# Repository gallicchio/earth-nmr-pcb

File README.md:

# Earth's Field NMR — a proton precession magnetometer on one board

Polarize the protons in a litre of water with a current through a coil, switch
the current off faster than they can follow, and listen: they precess about the
Earth's magnetic field at a couple of kilohertz and induce about a microvolt in the
same coil for a second or two.  This board does all of it — the polarizing switch,
the relay that hands the coil from the supply to the receiver, the tuned tank, a
low-noise preamplifier, the filters, the gain, and the sequencer that times it —
on a 243 x 150 mm, four layers printed circuit board whose silkscreen *is* the
schematic, with a headphone jack to hear the protons as well as see them.  Here in Claremont (Harvey Mudd, IGRF-14: 46.0 µT) the Larmor frequency
of the protons is 1960 Hz.

Every wire on the front is drawn on the silkscreen exactly where its copper runs;
every stage sits in a dashed box named for what it does; every node worth
looking at has a probe loop (26 of them, four of them ground).  The power rails
are planes, and each place a part meets one carries a ground symbol or a rail
flag, as a sheet carries a power symbol.

## What is on it

| block | what it does | parts |
|---|---|---|
| POLARIZING SUPPLY | 6-30 V, up to 3 A, from a battery or a bench supply | a resettable fuse, a reverse-polarity crowbar, a 33 V clamp, 470 µF, a lamp |
| COIL, K1 | at rest the coil is the tank's inductor; energized, the relay puts it across the supply and the switch | HFD3/12 DPDT relay, 3 A contacts |
| POLARIZING SWITCH | turns the coil's current on and, in 0.4 ms, off; the clamp takes the coil's energy at about 130 V | IRFS4227 (200 V) MOSFET, SMCJ100A clamp, 0.1 Ω sense resistor |
| TANK | tunes the coil to the protons: eight switches add binary-weighted C0G capacitance in 3.3 nF steps, to 841 nF | DSIC08 DIP switch, 20 C0G capacitors, a bidirectional clamp |
| CAL IN | a known test current into the tank, 1 µA per volt | BNC, 1 MΩ, 51 Ω |
| PREAMPLIFIER | three-op-amp instrumentation amplifier, x101 | OPA197 (U1-U3) |
| HIGH-PASS, LOW-PASS | 688 Hz to 4.2 kHz, fourth-order high-pass, second-order low-pass | OPA197 (U4-U6), Sallen-Key |
| GAIN, OUT | x21 or x201 more: x2121 (LOW) or x20301 (HIGH) from the tank to OUT | OPA197 (U7), a slide switch, BNC |
| HEADPHONES | the FID by ear: OUT through a VOLUME knob and a follower to both ears of a 3.5 mm stereo jack; about 30 mV, 81 dB SPL, in a 32 Ω earpiece at full volume on HIGH | ALPS RK09K 10k knob, OPA197 (U12), 100 Ω to each ear, Same Sky SJ1-3523N jack |
| SEQUENCER | polarize for 0.2-4.7 s, listen for 0.2-4.8 s; the relay closes first and opens last, so it never switches current | NE555, two TS391 comparators with RC delays, POLARIZE IN and SYNC OUT BNCs |
| POWER | ±15 V in, reverse-polarity diodes, clamps, lamps | |

## Using it

[docs/HANDBOOK.md](docs/HANDBOOK.md): what to wind for the coil, where to put it,
how to tune the tank for where you are, the bring-up in order with the expected
voltage at every probe loop, and the experiments (measuring the field, T2*, T1 by
the polarizing time).  The back of the board carries the short version.
**Caution:** the coil and Q1's drain swing to about 130 V for half a millisecond at
every switch-off.

## How it was designed

[docs/DESIGN_NOTES.md](docs/DESIGN_NOTES.md): why each block is what it is, the
arithmetic (`sim/design.py`, which writes `sim/design.json`: every value on the
sheet and the board comes from it), the simulation, the board, the risks for the
first board and the ideas for rev B.  [CLAUDE_CODE_CHAT.md](CLAUDE_CODE_CHAT.md)
is the conversation it came from.  `design_reviews/` holds the brief for
reviewers and the rounds run so far (the author's own, 2026-11-03).

## Ordering it

[docs/MANUFACTURING.md](docs/MANUFACTURING.md) is generated by the build: the files
to upload, JLCPCB's order form field by field, an estimate of the cost, and what to
look at in their placement preview.  The parts come to about $24 a board; every
part is stocked by JLCPCB.

## Building it

```bash
./make.py
```

runs, from `scripts/parts.py` and `sim/design.py` outward: the design arithmetic,
the symbols, footprints and 3D stand-ins, the schematic (`scripts/gen_sch.py`) and
its ERC, 393 circuit assertions on the exported netlist (`scripts/check_circuit.py`),
the ngspice simulation of that netlist (`sim/nmr_sim.py`: the tank, the receiver's
gain, band and noise, the switch-off, the sequencer and the headphones' level, each checked
against the arithmetic), the board (`scripts/layout.py`, laid out and wired by
`scripts/gen_pcb.py`, where every drawn wire is laid as copper) and its DRC with
schematic parity, the fab package and its checks (`scripts/check_outputs.py`), and
the generated documents, whose quoted numbers are checked against the build.
KiCad 10 and ngspice are needed; `./make.py --clean` removes what it generates.

## Files

- `hardware/` — the KiCad project (generated; do not edit by hand)
- `scripts/` — the generators and checkers
- `sim/` — the design arithmetic, the simulation and their results
- `out/earthnmr/` — gerbers, BOM, CPL, prints, assembly notes
- `docs/` — handbook, design notes, manufacturing, images
- `CLAUDE_CODE_CHAT.md` — how this was designed

## Licence

Hardware under CERN-OHL-P v2 (`LICENSE-HARDWARE.txt`), scripts under MIT
(`LICENSE`).  Jason Gallicchio and Claude, 2026.

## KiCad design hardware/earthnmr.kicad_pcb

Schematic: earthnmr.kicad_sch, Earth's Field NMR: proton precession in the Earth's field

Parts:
C1, C2: 100uF; CP_Elec_6.3x5.4; MPN JVJ25V100M6x5; LCSC C46550402
C3, C4, C54, C80, C81, C82, C83, C84, C85, C86, C87, C88, C89, C90, C91, C92, C93, C94, C95, C96, C97, C98, C99: 100nF; C_0805_2012Metric; MPN CC0805KRX7R9BB104; LCSC C49678
C5: 470uF; CP_Elec_10x12.5; MPN EFVM050ADA471M10C0; LCSC C22469994
C10, C13, C35: 3.3nF; C_0805_2012Metric; MPN 0805N332J101CT; LCSC C880847
C11, C16, C18, C20, C34: 6.8nF; C_0805_2012Metric; MPN CC0805JKNPO9BN682; LCSC C326913
C12, C14, C15, C23, C28, C29, C30, C31, C32, C33, C53: 10nF; C_0805_2012Metric; MPN 0805N103J500CT; LCSC C237168
C17: 47nF; C_1206_3216Metric; MPN C1206N473J050T; LCSC C5451690
C19, C21, C22, C24, C25, C26, C27, C55, C56: 100nF; C_1206_3216Metric; MPN 1206N104J500CT; LCSC C170182
C50, C51, C52: 1uF; C_Film_P5.00mm_L7.2mm_W6.0mm; MPN MES105J2A-7-50R0; LCSC C333829
D1, D2, D3, D4, D5: SS34; D_SMA; MPN SS34; LCSC C8678
D6: SMBJ33A; D_SMB; MPN SMBJ33A; LCSC C353366
D7: SMCJ100A; D_SMC; MPN SMCJ100A; LCSC C42371542
D8, D10, D11, D13, D14: 1N4148W; D_SOD-123; MPN 1N4148W; LCSC C81598
D9: SMBJ12CA; D_SMB; MPN SMBJ12CA; LCSC C353397
D12: BAT54S; SOT-23; MPN BAT54S,215; LCSC C47546
F1: 3A; Fuse_2920_7451Metric; MPN 2920L300/36GR; LCSC C22435908
J1: POWER; TerminalBlock_KF301_1x03_P5.00mm; MPN KF301-5.0-3P; LCSC C474882
J2: POLARIZE SUPPLY; TerminalBlock_KF301_1x02_P5.00mm; MPN KF301-5.0-2P; LCSC C474881
J3: COIL; TerminalBlock_KF301_1x03_P5.00mm; MPN KF301-5.0-3P; LCSC C474882
J4, J5, J7, J8: BNC; BNC_KYWE_RightAngle; MPN BNC-KYWE-295-W4-N; LCSC C41416668
J9: PHONES; Jack_3.5mm_CUI_SJ1-3523N_Horizontal; MPN SJ1-3523N; LCSC C20182914
K1: HFD3/12; Relay_DPDT_Omron_G6S-2; MPN HFD3/12; LCSC C329305
LED1, LED2, LED3: GREEN; LED_0805_2012Metric; MPN KT-0805G; LCSC C2297
LED4: RED; LED_0805_2012Metric; MPN NCD0805R1; LCSC C84256
MH1, MH2, MH3, MH4: MountingHole; MountingHole_3.2mm_M3
Q1: IRFS4227; TO-263-2; MPN IRFS4227TRLPBF; LCSC C146578
Q2, Q3: MMBT3904; SOT-23; MPN MMBT3904; LCSC C20526
R1, R2, R8, R9, R17, R18, R20, R21, R22, R23, R31, R44, R46, R48, R51, R52, R53, R54, R59: 10k; R_0805_2012Metric; MPN 0805W8F1002T5E; LCSC C17414
R3: 15k; R_0805_2012Metric; MPN 0805W8F1502T5E; LCSC C17475
R4: 0.1R; R_2512_6332Metric; MPN RLP25FEER100; LCSC C160587
R5: 47R; R_0805_2012Metric; MPN 0805W8F470JT5E; LCSC C17714
R6, R40, R41, R42, R43, R45: 100k; R_0805_2012Metric; MPN 0805W8F1003T5E; LCSC C149504
R7: 4.7k; R_0805_2012Metric; MPN 0805W8F4701T5E; LCSC C17673
R10: 3.3k; R_0805_2012Metric; MPN 0805W8F3301T5E; LCSC C26010
R11, R12, R14, R47: 1M; R_0805_2012Metric; MPN 0805W8F1004T5E; LCSC C17514
R13: 51R; R_0805_2012Metric; MPN 0805W8F510JT5E; LCSC C17738
R15, R16, R32, R33, R55: 1k; R_0805_2012Metric; MPN 0805W8F1001T5E; LCSC C17513
R19: 200R; R_0805_2012Metric; MPN 0805W8F2000T5E; LCSC C17540
R24: 20k; R_0805_2012Metric; MPN 0805W8F2002T5E; LCSC C4328
R25: 24k; R_0805_2012Metric; MPN 0805W8F2402T5E; LCSC C17575
R26: 9.1k; R_0805_2012Metric; MPN 0805W8F9101T5E; LCSC C17855
R27, R58: 62k; R_0805_2012Metric; MPN 0805W8F6202T5E; LCSC C17783
R28, R29: 8.2k; R_0805_2012Metric; MPN 0805W8F8201T5E; LCSC C17828
R30: 200k; R_0805_2012Metric; MPN 0805W8F2003T5E; LCSC C17539
R49: 220k; R_0805_2012Metric; MPN 0805W8F2203T5E; LCSC C17556
R50: 270k; R_0805_2012Metric; MPN 0805W8F2703T5E; LCSC C17589
R56, R57: 100R; R_0805_2012Metric; MPN 0805W8F1000T5E; LCSC C17408
RV1, RV2: 2M; Potentiometer_Bourns_3362P_Vertical; MPN 3362P-1-205; LCSC C48997907
RV3: 10k; Potentiometer_Alps_RK09K_Single_Vertical; MPN RK09K1130AAU; LCSC C202373
SW1: TUNE; SW_DIP_SPSTx08_Slide_KingTek_DSIC08LSGET_W8.61mm_P2.54mm; MPN DSIC08LSGET; LCSC C3293158
SW2: GAIN; SW_SPDT_Shouhan_MSK12C02; MPN MSK12C02; LCSC C431540
SW3: SEQUENCE; SW_SPDT_Shouhan_MSK12C02; MPN MSK12C02; LCSC C431540
SW4: MODE; SW_SPDT_Shouhan_MSK12C02; MPN MSK12C02; LCSC C431540
TP1: V POL; TestPoint_Loop_RH-5019; MPN RH-5019; LCSC C5199800
TP2: DRAIN; TestPoint_Loop_RH-5019; MPN RH-5019; LCSC C5199800
TP3: I POL; TestPoint_Loop_RH-5019; MPN RH-5019; LCSC C5199800
TP4: GATE; TestPoint_Loop_RH-5019; MPN RH-5019; LCSC C5199800
TP5: TANK+; TestPoint_Loop_RH-5019; MPN RH-5019; LCSC C5199800
TP6: TANK-; TestPoint_Loop_RH-5019; MPN RH-5019; LCSC C5199800
TP7: INA A; TestPoint_Loop_RH-5019; MPN RH-5019; LCSC C5199800
TP8: INA B; TestPoint_Loop_RH-5019; MPN RH-5019; LCSC C5199800
TP9: PREAMP; TestPoint_Loop_RH-5019; MPN RH-5019; LCSC C5199800
TP10: HP1; TestPoint_Loop_RH-5019; MPN RH-5019; LCSC C5199800
TP11: HP; TestPoint_Loop_RH-5019; MPN RH-5019; LCSC C5199800
TP12: LP; TestPoint_Loop_RH-5019; MPN RH-5019; LCSC C5199800
TP13: OUT; TestPoint_Loop_RH-5019; MPN RH-5019; LCSC C5199800
TP14: POL CMD; TestPoint_Loop_RH-5019; MPN RH-5019; LCSC C5199800
TP15: DELAY; TestPoint_Loop_RH-5019; MPN RH-5019; LCSC C5199800
TP16: HOLD; TestPoint_Loop_RH-5019; MPN RH-5019; LCSC C5199800
TP17: RELAY; TestPoint_Loop_RH-5019; MPN RH-5019; LCSC C5199800
TP18: TIMER; TestPoint_Loop_RH-5019; MPN RH-5019; LCSC C5199800
TP19: EXT; TestPoint_Loop_RH-5019; MPN RH-5019; LCSC C5199800
TP20: +15V; TestPoint_Loop_RH-5019; MPN RH-5019; LCSC C5199800
TP21: -15V; TestPoint_Loop_RH-5019; MPN RH-5019; LCSC C5199800
TP22: PHONES; TestPoint_Loop_RH-5019; MPN RH-5019; LCSC C5199800
TP100, TP101, TP102, TP103: GND; TestPoint_Loop_RH-5019; MPN RH-5019; LCSC C5199800
U1, U2, U3, U4, U5, U6, U7, U12: OPA197; SOT-23-5; MPN OPA197IDBVR; LCSC C221351
U8, U9, U10: TS391; SOT-23-5; MPN TS391ILT; LCSC C71896
U11: NE555; SOIC-8_3.9x4.9mm_P1.27mm; MPN NE555DR; LCSC C7593

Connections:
+15V: C1.1, C3.1, C80.1, C82.1, C84.1, C86.1, C88.1, C90.1, C92.1, C94.1, C95.1, C96.1, C97.1, C98.1, D1.1 (K), D3.1 (K), D8.1 (K), D12.2 (K), K1.1, Q3.3 (C), R1.1, R7.1, R9.1, R10.1, R40.1, R45.1, R48.1, R51.1, TP20.1, U1.5 (V+), U2.5 (V+), U3.5 (V+), U4.5 (V+), U5.5 (V+), U6.5 (V+), U7.5 (V+), U8.5 (V+), U9.5 (V+), U10.5 (V+), U11.4 (~RST), U11.8 (VCC), U12.5 (V+)
-15V: C2.2, C4.2, C81.1, C83.1, C85.1, C87.1, C89.1, C91.1, C93.1, C99.1, D2.2 (A), D4.2 (A), R2.2, TP21.1, U1.2 (V-), U2.2 (V-), U3.2 (V-), U4.2 (V-), U5.2 (V-), U6.2 (V-), U7.2 (V-), U12.2 (V-)
/+15V_IN: D1.2 (A), J1.1
/-15V_IN: D2.1 (K), J1.3
/COIL_A: J3.2, K1.4
/COIL_B: J3.1, K1.9
/DRAIN: D7.1 (K), K1.8, Q1.2 (D), TP2.1
/GATE: R5.1, R7.2, TP4.1, U9.1
/POL_CMD: D13.1 (K), D14.2 (A), R42.1, R49.1, R50.1, R53.1, SW4.2 (B), TP14.1
/SOURCE: D7.2 (A), Q1.3 (S), R4.1, R6.2, TP3.1
/TANK+: D9.2 (A2), K1.3, R14.2, R15.1, SW1.9, SW1.10, SW1.11, SW1.12, SW1.13, SW1.14, SW1.15, SW1.16, TP5.1
/TANK-: C10.2, C11.2, C12.2, C13.2, C14.2, C15.2, C16.2, C17.2, C18.2, C19.2, C20.2, C21.2, C22.2, C23.2, C24.2, C25.2, C26.2, C27.2, C28.2, C29.2, D9.1 (A1), K1.10, R16.1, TP6.1
/V_POL: C5.1, D5.1 (K), D6.1 (K), F1.2, K1.5, R3.1, TP1.1
GND: C1.2, C2.1, C3.2, C4.1, C5.2, C35.2, C50.2, C51.2, C52.2, C53.1, C54.2, C55.2, C56.2, C80.2, C81.2, C82.2, C83.2, C84.2, C85.2, C86.2, C87.2, C88.2, C89.2, C90.2, C91.2, C92.2, C93.2, C94.2, C95.2, C96.2, C97.2, C98.2, C99.2, D3.2 (A), D4.1 (K), D5.2 (A), D6.2 (A), D12.1 (A), J1.2, J2.2, J3.3, J4.2 (Ext), J5.2 (Ext), J7.2 (Ext), J8.2 (Ext), J9.S, LED1.1 (K), LED2.2 (A), LED3.1 (K), Q2.2 (E), R4.2, R11.1, R12.2, R13.2, R22.1, R25.2, R27.2, R31.1, R32.1, R42.2, R43.2, R46.2, R52.2, R54.2, RV3.1, SW4.3 (C), TP100.1, TP101.1, TP102.1, TP103.1, U8.2 (V-), U9.2 (V-), U10.2 (V-), U11.1 (GND)
unnamed: C10.1, SW1.1
unnamed: C11.1, SW1.2
unnamed: C12.1, C13.1, SW1.3
unnamed: C14.1, C15.1, C16.1, SW1.4
unnamed: C17.1, C18.1, SW1.5
unnamed: C19.1, C20.1, SW1.6
unnamed: C21.1, C22.1, C23.1, SW1.7
unnamed: C24.1, C25.1, C26.1, C27.1, C28.1, C29.1, SW1.8
unnamed: C30.1, R23.2, TP9.1, U3.1
unnamed: C30.2, C31.1, R24.1
unnamed: C32.2, C33.1, R26.1
unnamed: C34.1, R28.2, R29.1
unnamed: D8.2 (A), K1.12, LED4.1 (K), Q2.3 (C)
unnamed: D10.2 (A), RV1.2, RV1.3, RV2.1, U11.7 (DISCH)
unnamed: C50.1, C51.1, C52.1, D10.1 (K), D11.2 (A), TP18.1, U11.2 (TRIG), U11.6 (THRES)
unnamed: D11.1 (K), R41.2
unnamed: D12.3 (COM), R44.2, R47.1, R59.1
unnamed: C55.1, D13.2 (A), R49.2, TP15.1, U9.4 (+)
unnamed: C56.1, D14.1 (K), R50.2, TP16.1, U10.4 (+)
unnamed: F1.1, J2.1
unnamed: J4.1 (In), R13.1, R14.1
unnamed: J5.1 (In), R33.2
unnamed: J7.1 (In), R43.1, R44.1
unnamed: J8.1 (In), R55.2
unnamed: J9.R, R57.2
unnamed: J9.T, R56.2
unnamed: LED1.2 (A), R1.2
unnamed: LED2.1 (K), R2.1
unnamed: LED3.2 (A), R3.2
unnamed: LED4.2 (A), R10.2
unnamed: Q1.1 (G), R5.2, R6.1
unnamed: Q2.1 (B), R8.2
unnamed: Q3.1 (B), R53.2
unnamed: Q3.2 (E), R54.1, R55.1
unnamed: R8.1, R9.2, TP17.1, U10.1
unnamed: R17.2, R21.1, TP7.1, U1.1
unnamed: R18.2, R20.1, TP8.1, U2.1
unnamed: R30.2, R33.1, R58.1, TP13.1, U7.1
unnamed: R40.2, RV1.1
unnamed: R41.1, RV2.2, RV2.3
unnamed: R58.2, RV3.3
unnamed: R31.2, SW2.1 (A)
unnamed: R30.1, SW2.2 (B), U7.4 (-)
unnamed: R32.2, SW2.3 (C)
unnamed: R47.2, R48.2, SW3.1 (A), TP19.1, U8.1
unnamed: SW3.2 (B), SW4.1 (A)
unnamed: SW3.3 (C), U11.3 (OUT)
unnamed: R11.2, R15.2, U1.3 (+)
unnamed: R17.1, R19.1, U1.4 (-)
unnamed: R12.1, R16.2, U2.3 (+)
unnamed: R18.1, R19.2, U2.4 (-)
unnamed: R21.2, R22.2, U3.3 (+)
unnamed: R20.2, R23.1, U3.4 (-)
unnamed: C31.2, R25.1, U4.3 (+)
unnamed: C32.1, R24.2, TP10.1, U4.1, U4.4 (-)
unnamed: C33.2, R27.1, U5.3 (+)
unnamed: R26.2, R28.1, TP11.1, U5.1, U5.4 (-)
unnamed: C35.1, R29.2, U6.3 (+)
unnamed: C34.2, TP12.1, U6.1, U6.4 (-), U7.3 (+)
unnamed: R59.2, U8.4 (+)
unnamed: R45.2, R46.1, U8.3 (-)
unnamed: C54.1, R51.2, R52.1, U9.3 (-), U10.3 (-)
unnamed: C53.2, U11.5 (CONT)
unnamed: RV3.2, U12.3 (+)
unnamed: R56.1, R57.1, TP22.1, U12.1, U12.4 (-)

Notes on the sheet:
53.8n
gain 101 = 1 + 2 x 10k / 200R
follows POL CMD: 0 / 13 V open, through 1k;
the top of the band, and the anti-alias filter
film; t = 0.75 R C each way
3.3n
a x10 probe
off at once when it falls (D13)
the coil's energy here
A (2), B (1): the coil's two leads
on and ramping off
6.8n
3: LISTEN ONLY (no polarizing)
POL CMD low: the switch opens at once, the coil's current ramps off through D7, and the relay lets go 15 ms later (U10): LISTEN.
D12 clamps the input between -0.35 V and +15.3 V; R59 keeps
a function generator; ±30 V max;
1k in series: for a scope, an ADC
up to 130 V at switch-off:
POL CMD high = POLARIZE: the relay pulls in at once, and the switch closes 18 ms later (U9).
RV2 LISTEN TIME
13.3n
the TS391's pin inside its -0.3 V limit at ±30 V in
ground loops for the scope's clip
PREAMPLIFIER
constant current sets the coil's current;
Q 0.55 at 726 Hz and Q 1.31 at 670 Hz. 60 Hz -85 dB, 180 Hz -47 dB,
faster than the protons can follow
while the coil's current falls to zero in a
D9: a clamp, idle
Switch off: in a millisecond the field is gone, faster than the protons can follow, and they precess about the
S (3): its shield, if any
10-200 mH, up to 3 A, 1/2 L I^2 < 1 J
VOLUME
unless a fault dumps
a generator through 1M: I = V / 1M
for a sound card. C0G capacitors.
U8: a comparator at 1.3 V (R45, R46),
POLARIZE IN
1: EXT, the POLARIZE IN jack
x21 or x201 = 1 + 200k / Rg

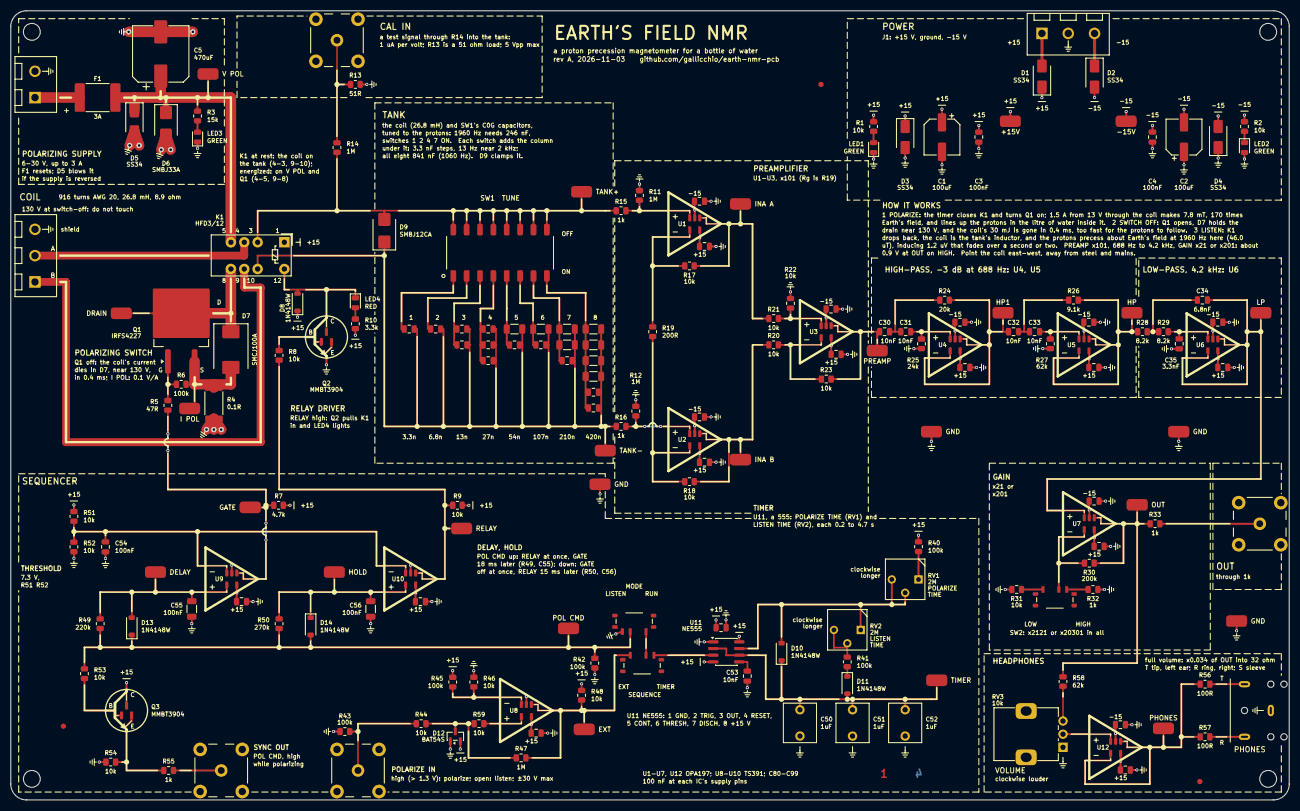
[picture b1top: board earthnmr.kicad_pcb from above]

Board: 4 copper layers, 243.0 x 150.0 mm, 191 parts (0 on the bottom side), 79 nets.

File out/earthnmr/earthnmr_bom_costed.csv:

Comment,Designator,Footprint,LCSC Part #,MPN,Qty,Unit $,Ext $,JLC
470uF,C5,CP_Elec_10x12.5,C22469994,EFVM050ADA471M10C0,1,0.1755,0.175,extended
47nF,C17,C_1206_3216Metric,C5451690,C1206N473J050T,1,0.1795,0.179,extended
100uF,"C1,C2",CP_Elec_6.3x5.4,C46550402,JVJ25V100M6x5,2,0.0423,0.085,extended
3.3nF,"C10,C13,C35",C_0805_2012Metric,C880847,0805N332J101CT,3,0.0214,0.064,extended
1uF,"C50,C51,C52",C_Film_P5.00mm_L7.2mm_W6.0mm,C333829,MES105J2A-7-50R0,3,0.1387,0.416,extended
6.8nF,"C11,C16,C18,C20,C34",C_0805_2012Metric,C326913,CC0805JKNPO9BN682,5,0.0904,0.452,extended
100nF,"C19,C21,C22,C24,C25,C26,C27,C55,C56",C_1206_3216Metric,C170182,1206N104J500CT,9,0.1580,1.422,extended
10nF,"C12,C14,C15,C23,C28,C29,C30,C31,C32,C33,C53",C_0805_2012Metric,C237168,0805N103J500CT,11,0.0302,0.332,extended
100nF,"C3,C4,C54,C80,C81,C82,C83,C84,C85,C86,C87,C88,C89,C90,C91,C92,C93,C94,C95,C96,C97,C98,C99",C_0805_2012Metric,C49678,CC0805KRX7R9BB104,23,0.0205,0.472,basic
SMBJ33A,D6,D_SMB,C353366,SMBJ33A,1,0.0404,0.040,extended
SMCJ100A,D7,D_SMC,C42371542,SMCJ100A,1,0.0916,0.092,preferred
SMBJ12CA,D9,D_SMB,C353397,SMBJ12CA,1,0.0409,0.041,extended
BAT54S,D12,SOT-23,C47546,"BAT54S,215",1,0.0283,0.028,basic
SS34,"D1,D2,D3,D4,D5",D_SMA,C8678,SS34,5,0.0352,0.176,basic
1N4148W,"D8,D10,D11,D13,D14",D_SOD-123,C81598,1N4148W,5,0.0124,0.062,basic
3A,F1,Fuse_2920_7451Metric,C22435908,2920L300/36GR,1,0.1851,0.185,extended
POWER,J1,TerminalBlock_KF301_1x03_P5.00mm,C474882,KF301-5.0-3P,1,0.1396,0.140,extended
POLARIZE SUPPLY,J2,TerminalBlock_KF301_1x02_P5.00mm,C474881,KF301-5.0-2P,1,0.1019,0.102,extended
COIL,J3,TerminalBlock_KF301_1x03_P5.00mm,C474882,KF301-5.0-3P,1,0.1396,0.140,extended
PHONES,J9,Jack_3.5mm_CUI_SJ1-3523N_Horizontal,C20182914,SJ1-3523N,1,1.2340,1.234,extended
BNC,"J4,J5,J7,J8",BNC_KYWE_RightAngle,C41416668,BNC-KYWE-295-W4-N,4,1.2929,5.172,extended
HFD3/12,K1,Relay_DPDT_Omron_G6S-2,C329305,HFD3/12,1,1.3894,1.389,extended
RED,LED4,LED_0805_2012Metric,C84256,NCD0805R1,1,0.0135,0.013,basic
GREEN,"LED1,LED2,LED3",LED_0805_2012Metric,C2297,KT-0805G,3,0.0164,0.049,basic
IRFS4227,Q1,TO-263-2,C146578,IRFS4227TRLPBF,1,0.8286,0.829,extended
MMBT3904,"Q2,Q3",SOT-23,C20526,MMBT3904,2,0.0117,0.023,basic
15k,R3,R_0805_2012Metric,C17475,0805W8F1502T5E,1,0.0059,0.006,basic
0.1R,R4,R_2512_6332Metric,C160587,RLP25FEER100,1,0.0571,0.057,extended
47R,R5,R_0805_2012Metric,C17714,0805W8F470JT5E,1,0.0029,0.003,basic
4.7k,R7,R_0805_2012Metric,C17673,0805W8F4701T5E,1,0.0039,0.004,basic
3.3k,R10,R_0805_2012Metric,C26010,0805W8F3301T5E,1,0.0043,0.004,basic
51R,R13,R_0805_2012Metric,C17738,0805W8F510JT5E,1,0.0030,0.003,basic
200R,R19,R_0805_2012Metric,C17540,0805W8F2000T5E,1,0.0068,0.007,basic
20k,R24,R_0805_2012Metric,C4328,0805W8F2002T5E,1,0.0042,0.004,basic
24k,R25,R_0805_2012Metric,C17575,0805W8F2402T5E,1,0.0044,0.004,basic
9.1k,R26,R_0805_2012Metric,C17855,0805W8F9101T5E,1,0.0030,0.003,preferred
200k,R30,R_0805_2012Metric,C17539,0805W8F2003T5E,1,0.0056,0.006,basic
220k,R49,R_0805_2012Metric,C17556,0805W8F2203T5E,1,0.0030,0.003,basic
270k,R50,R_0805_2012Metric,C17589,0805W8F2703T5E,1,0.0059,0.006,preferred
10k,RV3,Potentiometer_Alps_RK09K_Single_Vertical,C202373,RK09K1130AAU,1,0.6200,0.620,extended
62k,"R27,R58",R_0805_2012Metric,C17783,0805W8F6202T5E,2,0.0019,0.004,preferred
8.2k,"R28,R29",R_0805_2012Metric,C17828,0805W8F8201T5E,2,0.0027,0.005,basic
100R,"R56,R57",R_0805_2012Metric,C17408,0805W8F1000T5E,2,0.0042,0.008,basic
2M,"RV1,RV2",Potentiometer_Bourns_3362P_Vertical,C48997907,3362P-1-205,2,0.2394,0.479,extended
1M,"R11,R12,R14,R47",R_0805_2012Metric,C17514,0805W8F1004T5E,4,0.0044,0.018,basic
1k,"R15,R16,R32,R33,R55",R_0805_2012Metric,C17513,0805W8F1001T5E,5,0.0035,0.018,basic
100k,"R6,R40,R41,R42,R43,R45",R_0805_2012Metric,C149504,0805W8F1003T5E,6,0.0060,0.036,basic
10k,"R1,R2,R8,R9,R17,R18,R20,R21,R22,R23,R31,R44,R46,R48,R51,R52,R53,R54,R59",R_0805_2012Metric,C17414,0805W8F1002T5E,19,0.0034,0.065,basic
TUNE,SW1,SW_DIP_SPSTx08_Slide_KingTek_DSIC08LSGET_W8.61mm_P2.54mm,C3293158,DSIC08LSGET,1,0.4889,0.489,extended
GAIN,SW2,SW_SPDT_Shouhan_MSK12C02,C431540,MSK12C02,1,0.0544,0.054,extended
SEQUENCE,SW3,SW_SPDT_Shouhan_MSK12C02,C431540,MSK12C02,1,0.0544,0.054,extended
MODE,SW4,SW_SPDT_Shouhan_MSK12C02,C431540,MSK12C02,1,0.0544,0.054,extended
V POL,TP1,TestPoint_Loop_RH-5019,C5199800,RH-5019,1,0.0966,0.097,extended
DRAIN,TP2,TestPoint_Loop_RH-5019,C5199800,RH-5019,1,0.0966,0.097,extended
I POL,TP3,TestPoint_Loop_RH-5019,C5199800,RH-5019,1,0.0966,0.097,extended
GATE,TP4,TestPoint_Loop_RH-5019,C5199800,RH-5019,1,0.0966,0.097,extended
TANK+,TP5,TestPoint_Loop_RH-5019,C5199800,RH-5019,1,0.0966,0.097,extended
TANK-,TP6,TestPoint_Loop_RH-5019,C5199800,RH-5019,1,0.0966,0.097,extended
INA A,TP7,TestPoint_Loop_RH-5019,C5199800,RH-5019,1,0.0966,0.097,extended
INA B,TP8,TestPoint_Loop_RH-5019,C5199800,RH-5019,1,0.0966,0.097,extended
PREAMP,TP9,TestPoint_Loop_RH-5019,C5199800,RH-5019,1,0.0966,0.097,extended
HP1,TP10,TestPoint_Loop_RH-5019,C5199800,RH-5019,1,0.0966,0.097,extended
HP,TP11,TestPoint_Loop_RH-5019,C5199800,RH-5019,1,0.0966,0.097,extended
LP,TP12,TestPoint_Loop_RH-5019,C5199800,RH-5019,1,0.0966,0.097,extended
OUT,TP13,TestPoint_Loop_RH-5019,C5199800,RH-5019,1,0.0966,0.097,extended
POL CMD,TP14,TestPoint_Loop_RH-5019,C5199800,RH-5019,1,0.0966,0.097,extended
DELAY,TP15,TestPoint_Loop_RH-5019,C5199800,RH-5019,1,0.0966,0.097,extended
HOLD,TP16,TestPoint_Loop_RH-5019,C5199800,RH-5019,1,0.0966,0.097,extended
RELAY,TP17,TestPoint_Loop_RH-5019,C5199800,RH-5019,1,0.0966,0.097,extended
TIMER,TP18,TestPoint_Loop_RH-5019,C5199800,RH-5019,1,0.0966,0.097,extended
EXT,TP19,TestPoint_Loop_RH-5019,C5199800,RH-5019,1,0.0966,0.097,extended
+15V,TP20,TestPoint_Loop_RH-5019,C5199800,RH-5019,1,0.0966,0.097,extended
-15V,TP21,TestPoint_Loop_RH-5019,C5199800,RH-5019,1,0.0966,0.097,extended
PHONES,TP22,TestPoint_Loop_RH-5019,C5199800,RH-5019,1,0.0966,0.097,extended
GND,"TP100,TP101,TP102,TP103",TestPoint_Loop_RH-5019,C5199800,RH-5019,4,0.0966,0.386,extended
NE555,U11,SOIC-8_3.9x4.9mm_P1.27mm,C7593,NE555DR,1,0.1083,0.108,preferred
TS391,"U8,U9,U10",SOT-23-5,C71896,TS391ILT,3,0.1382,0.415,extended
OPA197,"U1,U2,U3,U4,U5,U6,U7,U12",SOT-23-5,C221351,OPA197IDBVR,8,0.7005,5.604,extended

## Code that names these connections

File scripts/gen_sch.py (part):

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    assert noA[1] < ncA[1] and ncB[1] < noB[1] and comA[0] < noA[0], (comA, noA, ncA, comB, ncB, noB)
    s.wire(j3a, (g(25), j3a[1]), (g(25), comA[1]), comA)
    s.wire(j3b, (g(23), j3b[1]), (g(23), comB[1]), comB)
    d.label("COIL_A", g(17), j3a[1])
    d.label("COIL_B", g(17), j3b[1])
    s.wire(noA, (XV, noA[1]), (XV, VPOL_Y))
    d.label("V_POL", XV - g(6), noA[1])
    d.text(["K1 HFD3/12: released, the coil LISTENS (as drawn);",
            "energized, it is POLARIZED:", "A to V POL, B to the switch"], POLE_X - g(6), YA - g(9.5), size=1.0)

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            ref_justify="left", val_justify="left")
    qg, qd, qs = s.pin("Q1", 1, "1"), s.pin("Q1", 1, "2"), s.pin("Q1", 1, "3")
    s.wire(noB, (qd[0], noB[1]), qd)
    d.label("DRAIN", noB[0] + g(0.5), noB[1])
    d.testpoint(qd[0], g(76), "DRAIN", rot=270, dx=3.4, dy=0.0)
    d.text(["DRAIN: up to 160 V,", "a x10 probe"], qd[0] + g(1.5), g(77.4), size=1.0)
    DCX = g(42)
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    s.wire((GATE_X, qg[1]), r5a)
    r6a, r6b = d.res("R6", D["gate"]["R_gs"], qg[0] - g(0.5), SRC_Y - g(1.5), side="left")
    s.wire(r6b, (qs[0] - g(1.5), SRC_Y), (qs[0], SRC_Y))
    d.label("SOURCE", qs[0] - g(1.2), SRC_Y)
    d.testpoint(qs[0] - g(1.5), SRC_Y, "I POL", rot=180, dx=-1.8, dy=3.6, justify="right")
    d.text(["I POL: 0.1 V per ampere,", "on and ramping off"], g(16), SRC_Y + g(2.4), size=1.0)

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    s.wire((PC_X, POLC_Y), r42a)
    d.gnd(*r42b)
    d.testpoint(PC_X + g(2), POLC_Y, "POL CMD", rot=0)
    d.label("POL_CMD", PC_X + g(3), POLC_Y)
    s.wire(b2, (PC_X, POLC_Y))

    # --- the threshold the two delays compare with: half the rail, on a bus
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    d.testpoint(ogx + g(2), og[1], "GATE", rot=180, dy=3.6)
    GATE_Y = g(112)
    s.wire((ogx, og[1]), (ogx + g(4), og[1]), (ogx + g(4), GATE_Y), (GATE_X, GATE_Y), (GATE_X, qg[1]))
    d.label("GATE", GATE_X + g(2), GATE_Y)
    # the relay: U10 out, 10k up, 10k into Q2's base; Q2 sinks the coil
    ohx = oh[0] + g(2)
    r9a, r9b = d.res("R9", "10k", ohx, oh[1] - g(3), side="right")
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

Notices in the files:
hardware/earthnmr.kicad_sch:
Open source, CERN-OHL-P-2.0 -- github.com/gallicchio/earth-nmr-pcb
scripts/gen_sch.py:
"Open source, CERN-OHL-P-2.0 -- " + parts.PROJECT_URL])
